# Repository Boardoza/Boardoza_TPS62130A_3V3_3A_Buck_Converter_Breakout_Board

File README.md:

# Boardoza TPS62130A 3A Buck Converter Breakout Board

The **Boardoza TPS62130A Breakout Board** is a compact and high-efficiency **3.3V buck (step-down) DC/DC converter** designed to deliver up to **3A output current** from a wide input voltage range. Based on the **Texas Instruments TPS62130A**, this board integrates advanced DCS-Control™ topology to provide excellent transient response, low output ripple, and high efficiency across load conditions.

With its ultra-low quiescent current and seamless Power Save Mode operation, this breakout board is ideal for **battery-powered systems as well as industrial and embedded applications**. It is perfect for powering microcontrollers, single-board computers, communication modules.

## [Click here to purchase!](https://www.ozdisan.com/ureticiler/boardoza)

| Front Side | Back Side |
|:---:|:---:|
|  |  |

---

## Key Features

- **Wide Input Range:** Accepts 4V to 17V input, suitable for common DC output.
- **High Output Capability:** Provides up to 3A continuous output current.
- **Fixed 3.3V Output:** Optimized for 3.3V digital systems.
- **High Efficiency Design:** DCS-Control™ topology ensures fast transient response and stable regulation.
- **Ultra-Low Quiescent Current:** Typical 17µA for low-power applications.    
- **Integrated Protections:** Includes short-circuit and thermal protection.

---

## Technical Specifications

**Model:** TPS62130A  
**Manufacturer:** Boardoza  
**Manufacturer IC:** Texas Instruments  
**Device Type:** Synchronous Step-Down (Buck) Converter  
**Topology:** DCS-Control™  
**Input Voltage:** 4V – 17V  
**Output Voltage:** 3.3V (Fixed)  
**Maximum Output Current:** 3A  
**Quiescent Current (IQ):** 17µA (typical)    
**Peak Efficiency:** Up to 95%  
**Typical Efficiency:** 90–94% (VIN = 12V, VOUT = 3.3V, medium load)  
**Operating Temperature:** -40°C to +150°C (IC)  
**Board Dimensions:** 20mm x 40mm  

---

## Board Pinout

### ( J1 ) Input Connector

| Pin Number | Pin Name | Description |
|:---:|:---:|---|
| 1 | VIN | Input Voltage (4V – 17V) |
| 2 | GND | Ground |

### ( J2 ) Output Connector

| Pin Number | Pin Name | Description |
|:---:|:---:|---|
| 1 | VOUT | Regulated 3.3V Output |
| 2 | GND | Ground |

---

## Board Dimensions

---

## Step Files

[Boardoza TPS62130A.step](./assets/TPS62130A_3V3%20Step.step)

---

## Datasheet

[TPS62130A Datasheet.pdf](./assets/TPS62130A_3V3%20Datasheet.pdf)

---

## Version History

- V1.0.0 - Initial Release

---

## Support

- If you have any questions or need support, please contact <support@boardoza.com>

---

## **License**
### **Hardware Design**

[![CC BY-SA 4.0][cc-by-sa-shield]][cc-by-sa]

All hardware design files are licensed under [Creative Commons Attribution-ShareAlike 4.0 International License][cc-by-sa].

[cc-by-sa]: http://creativecommons.org/licenses/by-sa/4.0/
[cc-by-sa-shield]: https://img.shields.io/badge/License-CC%20BY--SA%204.0-lightgrey.svg

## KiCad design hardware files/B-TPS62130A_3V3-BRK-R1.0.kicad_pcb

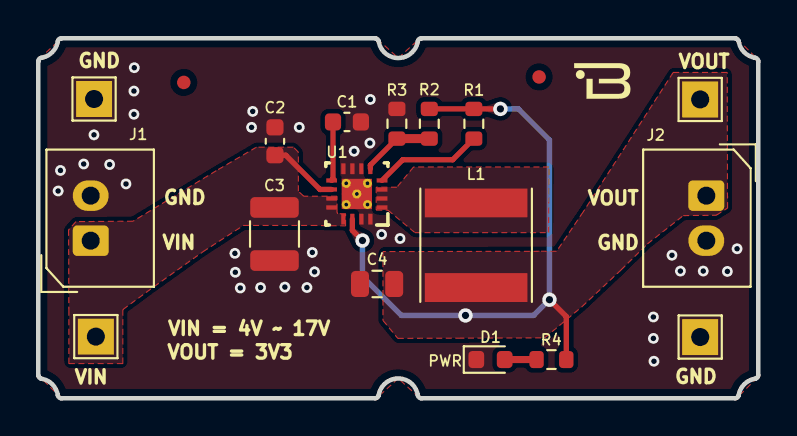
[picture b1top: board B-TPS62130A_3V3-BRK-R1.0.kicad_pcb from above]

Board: 2 copper layers, 40.0 x 20.0 mm, 19 parts (0 on the bottom side), 8 nets.

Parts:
C1: 3.3nF; C_0603_1608Metric
C2: 0.1uF; C_0603_1608Metric
C3: 10uF; C_1210_3225Metric
C4: 22uF; C_0805_2012Metric
D1: RED; LED_0603_1608Metric
FID1, FID2: Fiducial; Fiducial_0.75mm_Mask1.5mm
J1, J2: Conn_01x02; 2317-02S_1x02_P2.50mm_Vertical
J3, J4: GND; TestPoint_THTPad_2.0x2.0mm_Drill1.0mm
J5: VIN; TestPoint_THTPad_2.0x2.0mm_Drill1.0mm
J6: VOUT; TestPoint_THTPad_2.0x2.0mm_Drill1.0mm
L1: 2.2uH; L_Taiyo-Yuden_NR-60xx
R1: 100K; R_0603_1608Metric
R2: 1.21M; R_0603_1608Metric
R3: 383K; R_0603_1608Metric
R4: 10K; R_0603_1608Metric
U1: TPS62130ARGTR; RGT0016C

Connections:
/VIN: C2.2, C3.2, J1.1, J5.1, U1.10 (AVIN), U1.11 (PVIN), U1.12 (PVIN), U1.13 (EN)
/VOUT: C4.2, J2.1, J6.1, L1.2, R1.1, R2.1, R4.1, U1.14 (VOS)
GND: C1.1, C2.1, C3.1, C4.1, D1.1 (K), J1.2, J2.2, J3.1, J4.1, R3.2, U1.6 (AGND), U1.7 (FSW), U1.8 (DEF), U1.15 (PGND), U1.16 (PGND), U1.17 (EP), U1.18 (MP1), U1.19 (MP2), U1.20 (MP3), U1.21 (MP4), U1.22 (MP5)
unnamed: D1.2 (A), R4.2
unnamed: L1.1, U1.1 (SW), U1.2 (SW), U1.3 (SW)
unnamed: R2.2, R3.1, U1.5 (FB)
unnamed: R1.2, U1.4 (PG)
unnamed: C1.2, U1.9 (SS_TR)
